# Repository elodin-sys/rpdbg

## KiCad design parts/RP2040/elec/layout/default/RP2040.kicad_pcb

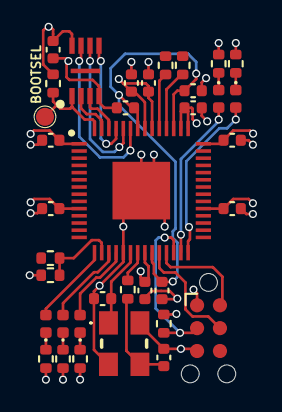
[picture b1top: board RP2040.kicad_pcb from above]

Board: 4 copper layers, 36 parts (0 on the bottom side), 28 nets.

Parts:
C1, C2: 50V 15pF C0G ±5% 0402 Multilayer Ceramic Capacito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; C0402
C3, C4: 25V 1uF X5R ±10% 0402 Multilayer Ceramic Capacito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; C0402
C5, C6, C7, C8, C9, C10, C11, C12, C13, C14: 16V 100nF X7R ±10% 0402 Multilayer Ceramic Capaci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; C0402
LED1, LED2, LED3, LED4, LED5: ?; LED_0402_1005Metric
R1: 62.5mW Thick Film Resistors 50V ±100ppm/℃ ±1% 5.6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; R0402
R2, R6, R7: 62.5mW Thick Film Resistors 50V ±100ppm/℃ ±1% 10k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; R0402
R3, R4: 62.5mW Thick Film Resistors 50V ±100ppm/℃ ±1% 27Ω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; R0402
R5: 62.5mW Thick Film Resistors 50V ±100ppm/℃ ±1% 1kΩ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; R0402
R8, R9, R10: 62.5mW Thick Film Resistors 50V ±100ppm/℃ ±1% 330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; R0402
R11, R12: 62.5mW Thick Film Resistors 50V ±100ppm/℃ ±1% 220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; R0402
T1: ?; TestPoint_Pad_D1.0mm
U1: Microcontroller in QFN Package; QFN40P700X700X90-57N-D
U2: ?; Tag-Connect_TC2030-IDC-NL_2x03_P1.27mm_Vertical
U3: Crystal, 12 MHz, SMD, 3.2mm x 2.5mm, 30 ppm, 10 p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; ABM8272T3
U4: NOR Flash spiFlash, 3V, 16M-bit, 4Kb Uniform Sect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; SON50P300X200X60-9N

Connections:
cs: R6.2, T1.1, U1.56, U4.1
gpio12: LED1.2, U1.15
gpio13: R1.2, R2.1, U1.16
gpio14: LED2.2, U1.17
gpio15: LED3.2, U1.18
gpio16: LED4.2, U1.27
gpio17: LED5.2, U1.28
io0: U1.53, U4.5
io1: U1.55, U4.2
io2: U1.54, U4.3
io3: U1.51, U4.7
mcu.led_amber_0.resistor-cathode: LED1.1, R8.1
mcu.led_amber_1.resistor-cathode: LED2.1, R9.1
mcu.led_amber_2.resistor-cathode: LED3.1, R10.1
mcu.led_green_0.resistor-cathode: LED4.1, R11.1
mcu.led_green_1.resistor-cathode: LED5.1, R12.1
mcu.mcu-gnd: C1.2, C2.2, C3.2, C4.2, C5.2, C6.2, C7.2, C8.2, C9.2, C10.2, C11.2, C12.2, C13.2, C14.2, R2.2, R8.2, R9.2, R10.2, R11.2, R12.2, U1.19, U1.57, U2.5, U3.2, U3.4, U4.4
mcu.mcu-vcc: C3.1, C7.1, C8.1, C9.1, C10.1, C11.1, C12.1, C13.1, C14.1, R6.1, R7.1, U1.1, U1.10, U1.22, U1.33, U1.42, U1.43, U1.44, U1.48, U1.49, U2.1, U4.8
mcu.mcu-vcc-1: C4.1, C5.1, C6.1, U1.23, U1.45, U1.50
out: C2.1, R5.2, U3.3
run: R7.2, U1.26, U2.3
sck: U1.52, U4.6
swclk: U1.24, U2.4
swdio: U1.25, U2.2
usb_dm: R4.2, U1.46
usb_dp: R3.1, U1.47
xin: C1.1, U1.20, U3.1
xout: R5.1, U1.21

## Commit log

2024-12-31 Add RP2040
